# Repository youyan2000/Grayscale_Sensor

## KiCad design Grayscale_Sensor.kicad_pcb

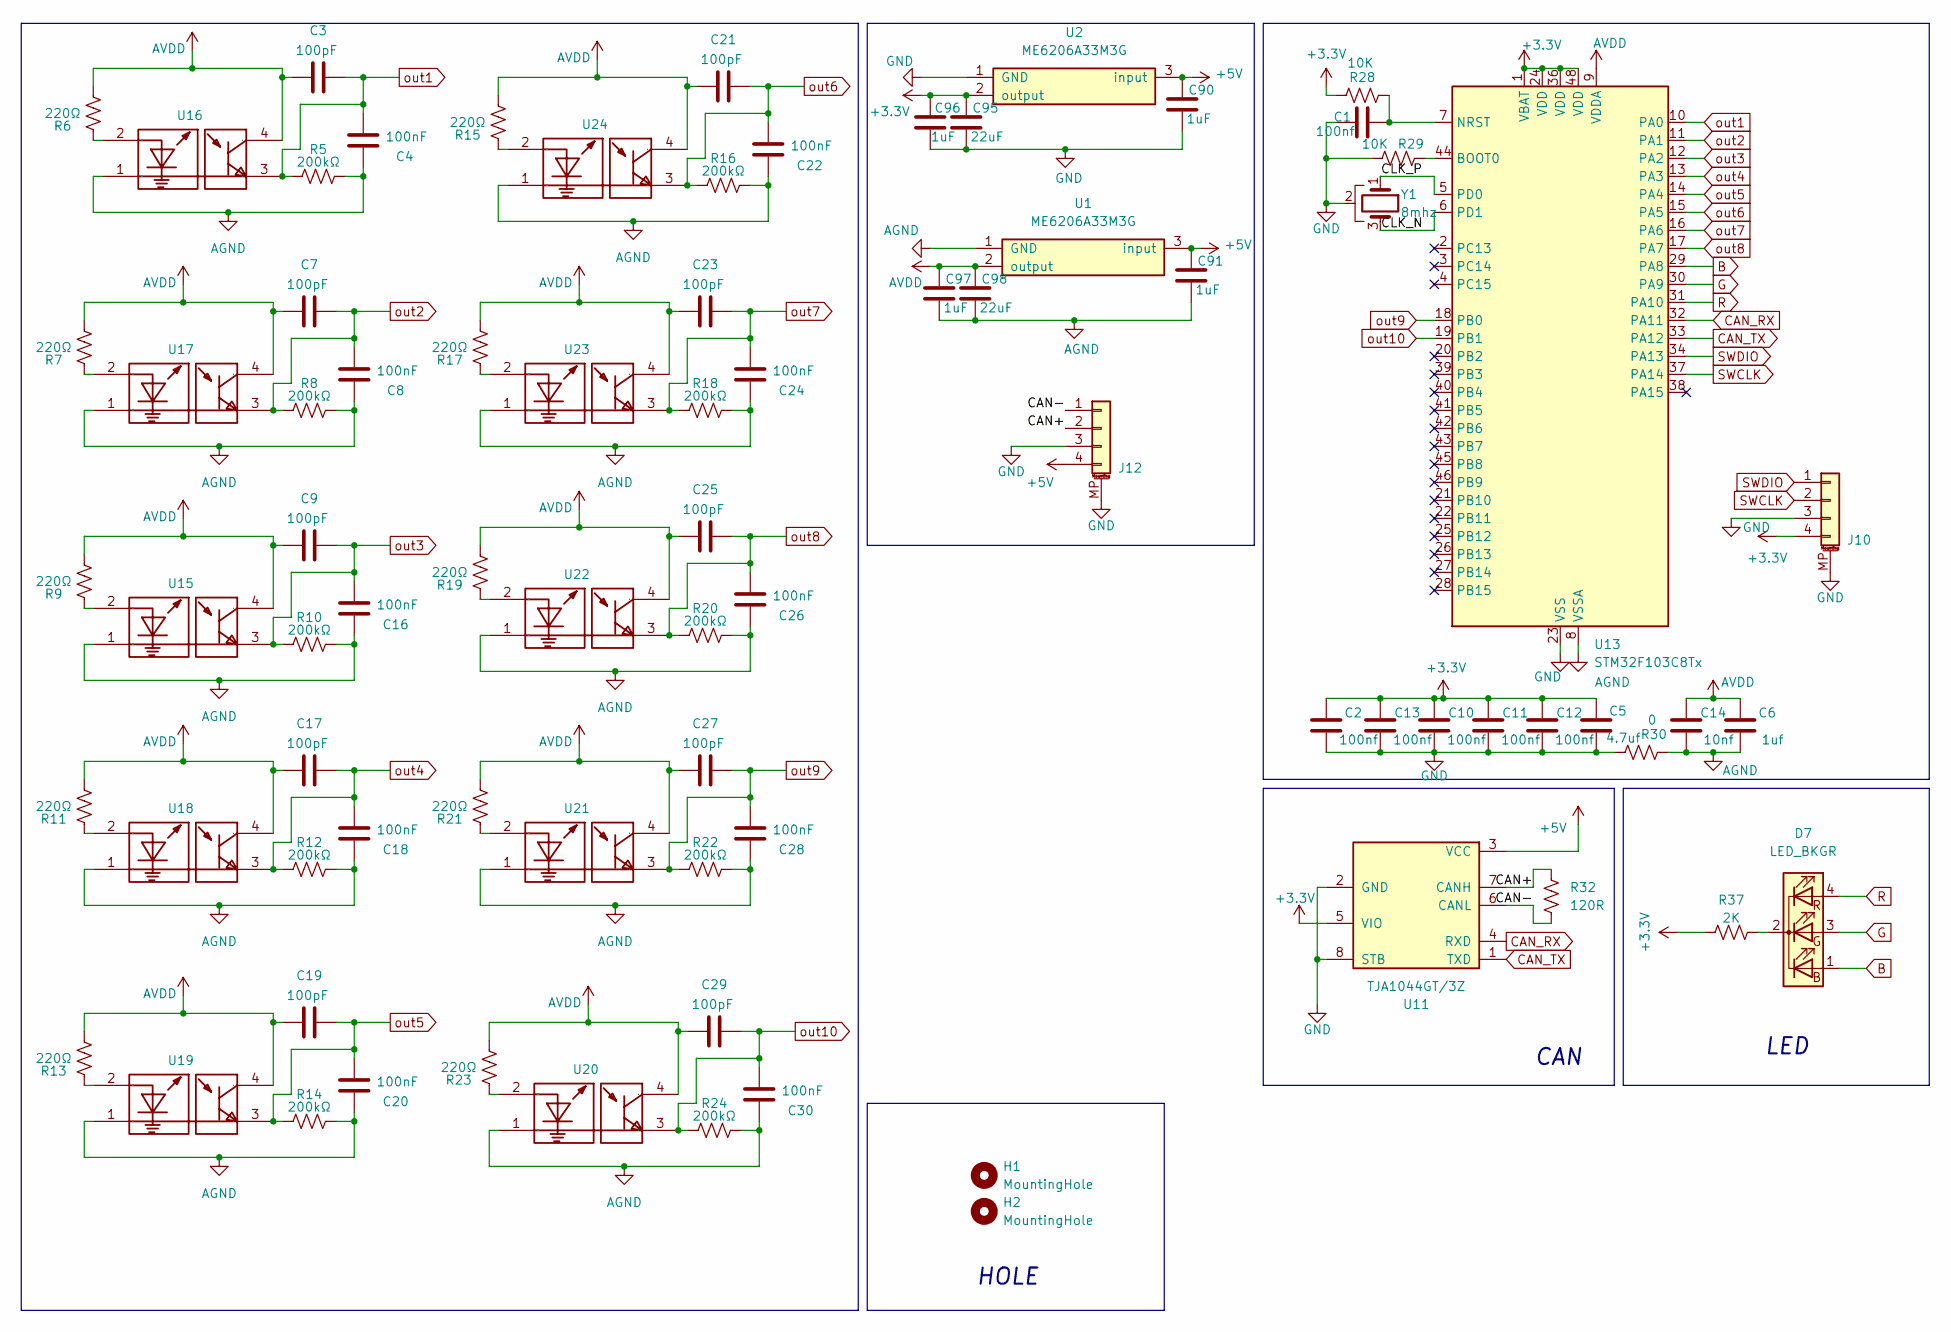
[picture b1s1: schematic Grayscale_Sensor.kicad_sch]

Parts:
C1, C2, C10, C11, C12, C13: 100nf; C_0603_1608Metric_Pad1.08x0.95mm_HandSolder
C3, C7, C9, C17, C19, C21, C23, C25, C27, C29: 100pF; C_0603_1608Metric
C4, C8, C16, C18, C20, C22, C24, C26, C28, C30: 100nF; C_0603_1608Metric
C5: 4.7uf; C_0603_1608Metric_Pad1.08x0.95mm_HandSolder
C6: 1uf; C_0603_1608Metric_Pad1.08x0.95mm_HandSolder
C14: 10nf; C_0603_1608Metric_Pad1.08x0.95mm_HandSolder
C90, C91, C96, C97: 1uF; C_0805_2012Metric
C95, C98: 22uF; C_0805_2012Metric
D7: LED_BKGR; LED_RGB_1210
H1, H2: MountingHole; MountingHole_3.2mm_M3
J10, J12: Conn_01x04; Molex_CLIK-Mate_502386-0470_1x04-1MP_P1.25mm_Horizontal
R5, R8, R10, R12, R14, R16, R18, R20, R22, R24: 200kΩ; R_0603_1608Metric
R6, R7, R9, R11, R13, R15, R17, R19, R21, R23: 220Ω; R_0603_1608Metric
R28: 10K; R_0603_1608Metric
R29: 10K; R_0603_1608Metric_Pad0.98x0.95mm_HandSolder
R30: 0; R_0603_1608Metric
R32: 120R; R_0603_1608Metric_Pad0.98x0.95mm_HandSolder
R37: 2K; R_0603_1608Metric_Pad0.98x0.95mm_HandSolder
U1, U2: ME6206A33M3G; MPN ME6206A33M3G
U11: TJA1044GT/3Z; SOIC-8_3.9x4.9mm_P1.27mm; MPN TJA1044GT/3Z
U13: STM32F103C8Tx; LQFP-48_7x7mm_P0.5mm
U15, U16, U17, U18, U19, U20, U21, U22, U23, U24: QRE1113GR; Manufacturer Part 灰度对管; LCSC Part Name ITR9909
Y1: 8mhz; CSTCE24M_3.2x1.3mm

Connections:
+3.3V: C2.1, C5.1, C10.1, C11.1, C12.1, C13.1, C95.1, C96.1, J10.4, R28.1, R37.2, U2.2 (output), U11.5 (VIO), U13.1 (VBAT), U13.24 (VDD), U13.36 (VDD), U13.48 (VDD)
+5V: C90.1, C91.1, J12.4, U1.3 (input), U2.3 (input), U11.3 (VCC)
/CAN+: J12.2, R32.2, U11.7 (CANH)
/CAN-: J12.1, R32.1, U11.6 (CANL)
/CLK_N: U13.6 (PD1), Y1.3
/CLK_P: U13.5 (PD0), Y1.1
AGND: C4.1, C6.2, C8.1, C14.2, C16.1, C18.1, C20.1, C22.1, C24.1, C26.1, C28.1, C30.1, C91.2, C97.2, C98.2, R5.2, R8.2, R10.2, R12.2, R14.2, R16.2, R18.2, R20.2, R22.2, R24.2, R30.2, U1.1 (GND), U13.8 (VSSA), U15.1, U16.1, U17.1, U18.1, U19.1, U20.1, U21.1, U22.1, U23.1, U24.1
AVDD: C3.1, C6.1, C7.1, C9.1, C14.1, C17.1, C19.1, C21.1, C23.1, C25.1, C27.1, C29.1, C97.1, C98.1, R6.2, R7.2, R9.2, R11.2, R13.2, R15.2, R17.2, R19.2, R21.2, R23.2, U1.2 (output), U13.9 (VDDA), U15.4, U16.4, U17.4, U18.4, U19.4, U20.4, U21.4, U22.4, U23.4, U24.4
B: D7.1 (BA), U13.29 (PA8)
CAN_RX: U11.4 (RXD), U13.32 (PA11)
CAN_TX: U11.1 (TXD), U13.33 (PA12)
G: D7.3 (GA), U13.30 (PA9)
GND: C1.2, C2.2, C5.2, C10.2, C11.2, C12.2, C13.2, C90.2, C95.2, C96.2, J10.3, J10.MP (MountPin), J12.3, J12.MP (MountPin), R29.2, R30.1, U2.1 (GND), U11.2 (GND), U11.8 (STB), U13.23 (VSS), U13.35 (VSS), U13.47 (VSS), Y1.2
unnamed: D7.2 (K), R37.1
unnamed: R6.1, U16.2
unnamed: R7.1, U17.2
unnamed: R9.1, U15.2
unnamed: R11.1, U18.2
unnamed: R13.1, U19.2
unnamed: R15.1, U24.2
unnamed: R17.1, U23.2
unnamed: R19.1, U22.2
unnamed: R21.1, U21.2
unnamed: R23.1, U20.2
unnamed: R29.1, U13.44 (BOOT0)
unnamed: C1.1, R28.2, U13.7 (NRST)
R: D7.4 (RA), U13.31 (PA10)
SWCLK: J10.2, U13.37 (PA14)
SWDIO: J10.1, U13.34 (PA13)
out1: C3.2, C4.2, R5.1, U13.10 (PA0), U16.3
out2: C7.2, C8.2, R8.1, U13.11 (PA1), U17.3
out3: C9.2, C16.2, R10.1, U13.12 (PA2), U15.3
out4: C17.2, C18.2, R12.1, U13.13 (PA3), U18.3
out5: C19.2, C20.2, R14.1, U13.14 (PA4), U19.3
out6: C21.2, C22.2, R16.1, U13.15 (PA5), U24.3
out7: C23.2, C24.2, R18.1, U13.16 (PA6), U23.3
out8: C25.2, C26.2, R20.1, U13.17 (PA7), U22.3
out9: C27.2, C28.2, R22.1, U13.18 (PB0), U21.3
out10: C29.2, C30.2, R24.1, U13.19 (PB1), U20.3

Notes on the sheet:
HOLE
CAN
LED

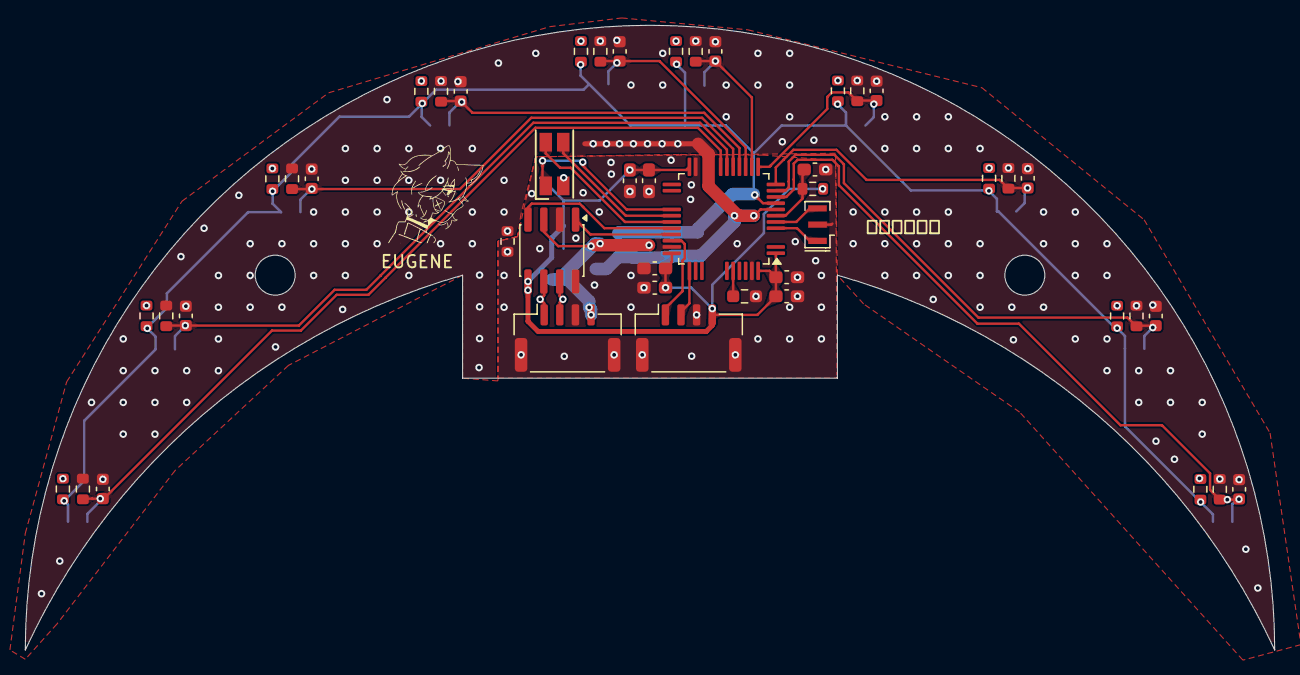
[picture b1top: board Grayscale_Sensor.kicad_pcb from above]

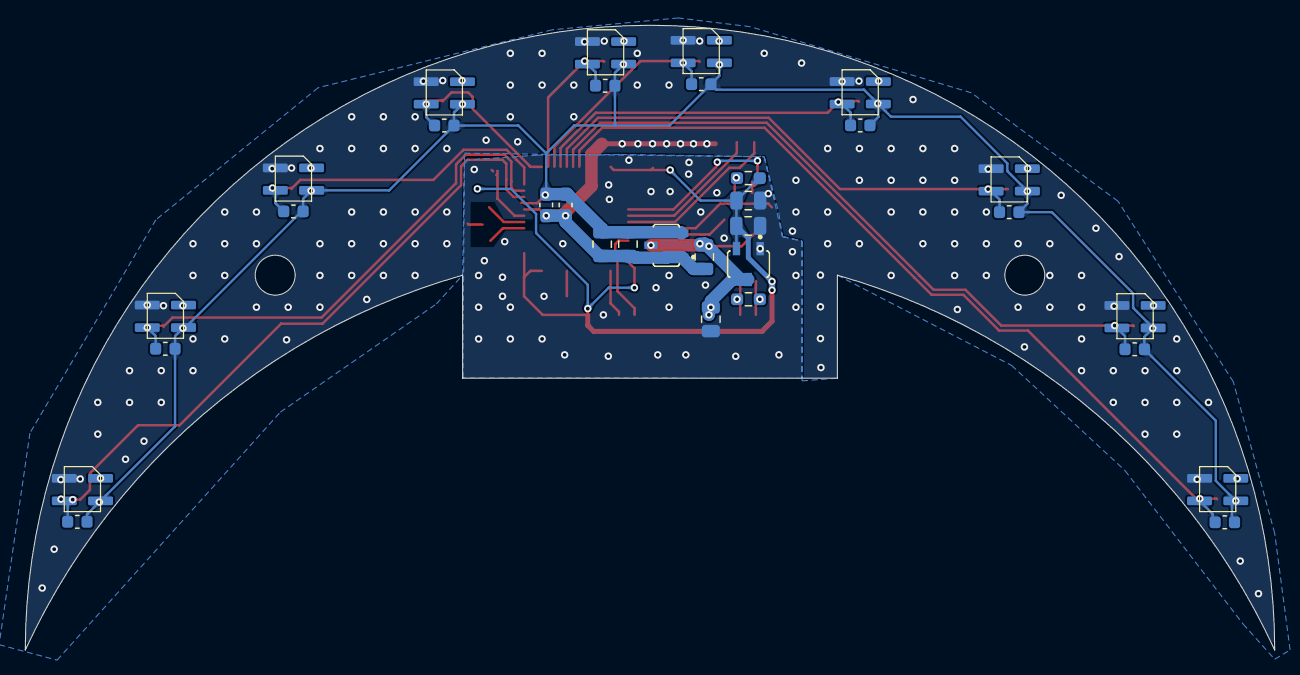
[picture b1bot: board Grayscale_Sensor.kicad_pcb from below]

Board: 2 copper layers, 100.0 x 50.0 mm, 80 parts (32 on the bottom side), 39 nets.
